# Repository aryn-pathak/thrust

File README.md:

# THRUST Freestyle drone and FC

## THRUST is an open source, sleek, lightweight, entry level FPV freestyle drone, powered by the custom THRUST FC made from scratch.

### THE THRUST MK1:

**A high speed drone, in a minimalistic yet striking frame, built for agility and a comfortable flying feel.**

### THE THRUST FC:

**Built to beat inaccesible, expensive, and capitalist FCs, at almost 1/6th the price of an average commercial FC, with the same perfomance, based on STM32F401CCU6, package of 40x31mm.**

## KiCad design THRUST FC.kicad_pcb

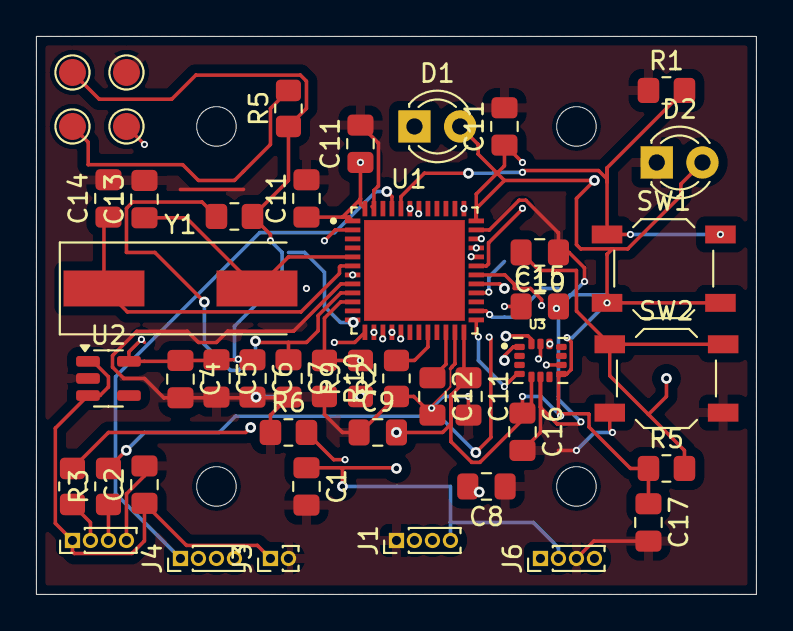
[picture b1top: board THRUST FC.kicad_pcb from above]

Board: 4 copper layers, 40.0 x 31.0 mm, 42 parts (0 on the bottom side), 29 nets.

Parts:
C1, C6: 10 µF; C_0805_2012Metric_Pad1.18x1.45mm_HandSolder
C2: 10uF; C_0805_2012Metric_Pad1.18x1.45mm_HandSolder
C4, C8, C9, C10, C11, C11#2, C11#3, C11#4, C15, C16: 0.1 µF; C_0805_2012Metric_Pad1.18x1.45mm_HandSolder
C5, C7, C17: 1 µF; C_0805_2012Metric_Pad1.18x1.45mm_HandSolder
C12: 2.2µF; C_0805_2012Metric_Pad1.18x1.45mm_HandSolder
C13, C14: 18pF; C_0805_2012Metric_Pad1.18x1.45mm_HandSolder
D1, D2: LED; LED_D3.0mm
J1, J2, J6: Conn_01x04_Pin; PinHeader_1x04_P1.00mm_Vertical
J3: Conn_01x02_Pin; PinHeader_1x02_P1.00mm_Vertical
J4: ESC; PinHeader_1x04_P1.00mm_Vertical
L1: L; R_0805_2012Metric_Pad1.20x1.40mm_HandSolder
R1, R2, R5, R5#2, R6, R9, R10: 10k; R_0805_2012Metric_Pad1.20x1.40mm_HandSolder
R3, R4: 22; R_0805_2012Metric_Pad1.20x1.40mm_HandSolder
SW1, SW2: SW_Push; SW_SPST_TL3342
U1: STM32F401CCU6; QFN50P700X700X60-49N
U2: AP2112K-3.3; SOT-23-5
U3: ICM-42688-P; PQFN50P300X250X97-14N
Y1: Crystal; Crystal_SMD_HC49-SD

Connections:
+5V: C2.1, C8.2, J2.1, J3.1, R9.1, U2.1 (VIN), U2.3 (EN)
ADC: C15.1, R9.2, R10.1, U1.10 (PA0)
BOOT0: R1.2, SW1.1, U1.44 (BOOT0)
D+: J2.3, R3.1
D-: J2.2, R4.1
GND: C1.2, C2.2, C4.2, C5.2, C6.2, C7.2, C8.1, C9.1, C10.1, C11.2, C11#2.2, C11#3.2, C11#4.2, C12.2, C13.2, C14.2, C15.2, C16.2, C17.2, D2.1 (K), J1.1, J2.4, J3.2, J6.3, R1.1, R2.1, R6.1, R10.2, SW2.2, U1.8 (VSSA/VREF-), U1.23 (VSS), U1.35 (VSS), U1.47 (VSS), U2.2 (GND), U3.6 (GND)
M1: J4.4, U1.29 (PA8)
M2: J4.3, U1.30 (PA9)
M3: J4.2, U1.31 (PA10)
M4: J4.1, U1.45 (PB8)
NRST: C10.2, R5.2, SW2.1, U1.7 (~RST)
unnamed: C13.1, U1.5 (PH0-OSC_IN), Y1.2
unnamed: C14.1, U1.6 (PH1-OSC_OUT), Y1.1
unnamed: R6.2, U3.9 (INT2/FSYNC/CLKIN)
PA4: U1.14 (PA4), U3.12 (AP_CS)
PA5: U1.15 (PA5), U3.13 (AP_SCL/AP_SCLK)
PA6: U1.16 (PA6), U3.1 (AP_SDO/AP_AD0)
PA7: U1.17 (PA7), U3.14 (AP_SDA/AP_SDIO/AP_SDI)
PA11: R4.2, U1.32 (PA11)
PA12: R3.2, U1.33 (PA12)
PB2: R2.2, U1.20 (PB2)
PC13: D1.1 (K), U1.2 (PC13)
SCL: J6.1, U1.42 (PB6)
SDA: J6.4, U1.43 (PB7)
SWCLK: J1.2, U1.37 (PA14/JTCK-SWCLK)
SWDIO: J1.3, U1.34 (PA13/JTMS-SWDIO)
VCAP1: C12.1, U1.22 (VCAP_1)
VDD: C1.1, C4.1, C5.1, C6.1, C9.2, C11.1, C11#2.1, C11#3.1, C11#4.1, C16.1, C17.1, D1.2 (A), D2.2 (A), J1.4, J6.2, L1.2, R5.1, R5#2.1, SW1.2, U1.1 (VBAT), U1.24 (VDD), U1.36 (VDD), U1.48 (VDD), U2.5 (VOUT), U3.5 (VDDIO), U3.8 (VDD)
VREF+: C7.1, L1.1, U1.9 (VDDA/VREF+)
